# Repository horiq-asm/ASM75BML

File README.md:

HILO8Lを使ってRSTP　wifiカメラ映像で推論を試しました。<br>
python basic_pipelines/detection_s0.py   -i "rtsp://user:passwd@192.168.10.224/stream2"<br>
raspberry pi CM5 搭載基板データです。<br>
Kicadの書式で作成しています。<br>
完成基板の動作はyoutubeでご覧ください<br>
https://youtu.be/_k28zdBtKoo　<br>

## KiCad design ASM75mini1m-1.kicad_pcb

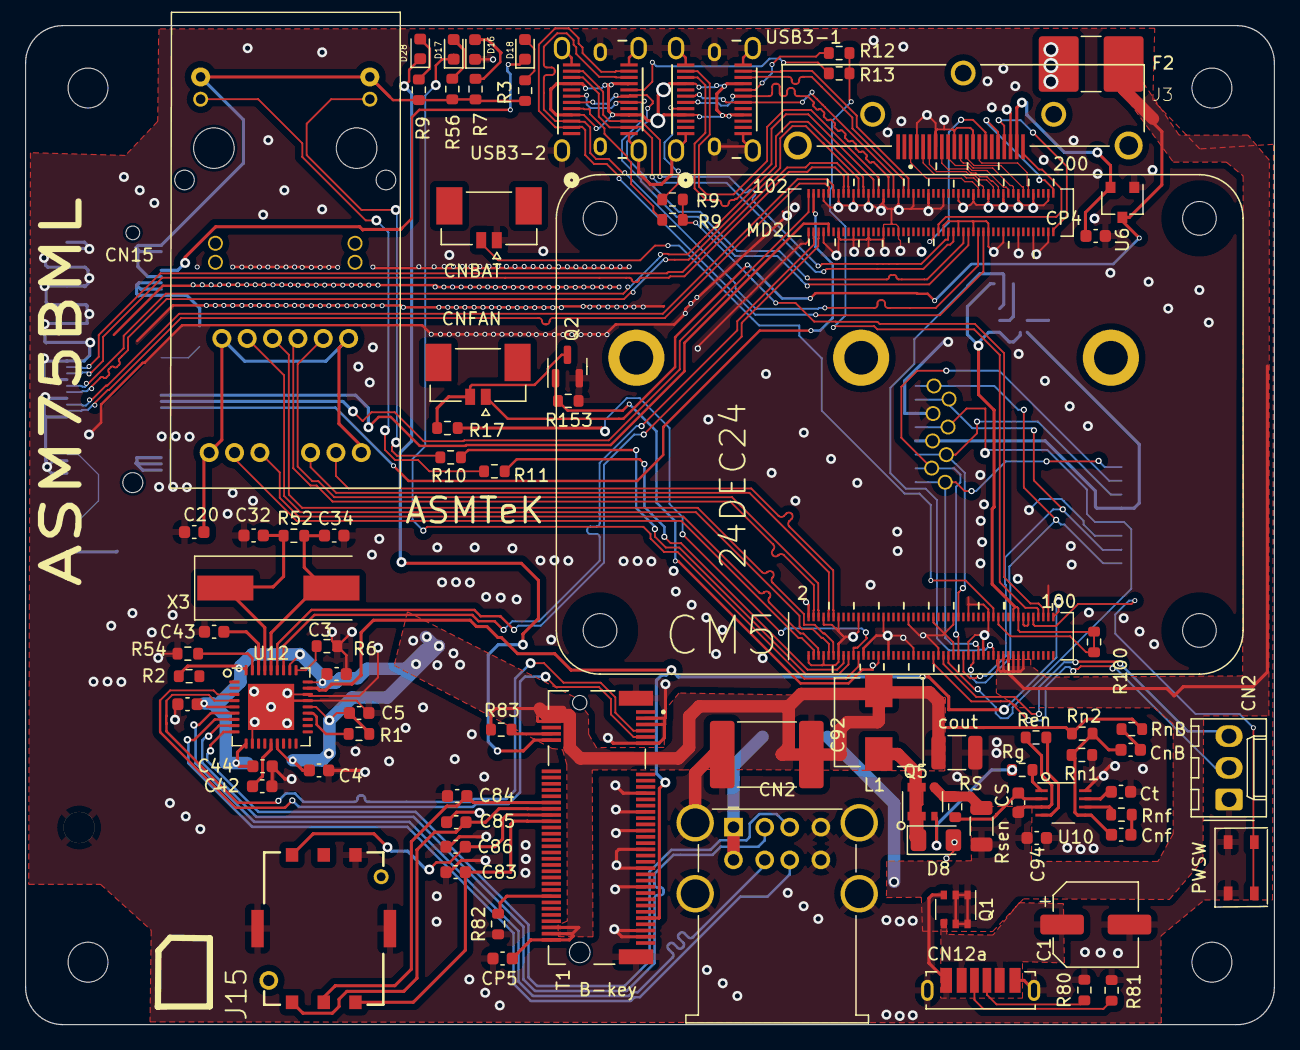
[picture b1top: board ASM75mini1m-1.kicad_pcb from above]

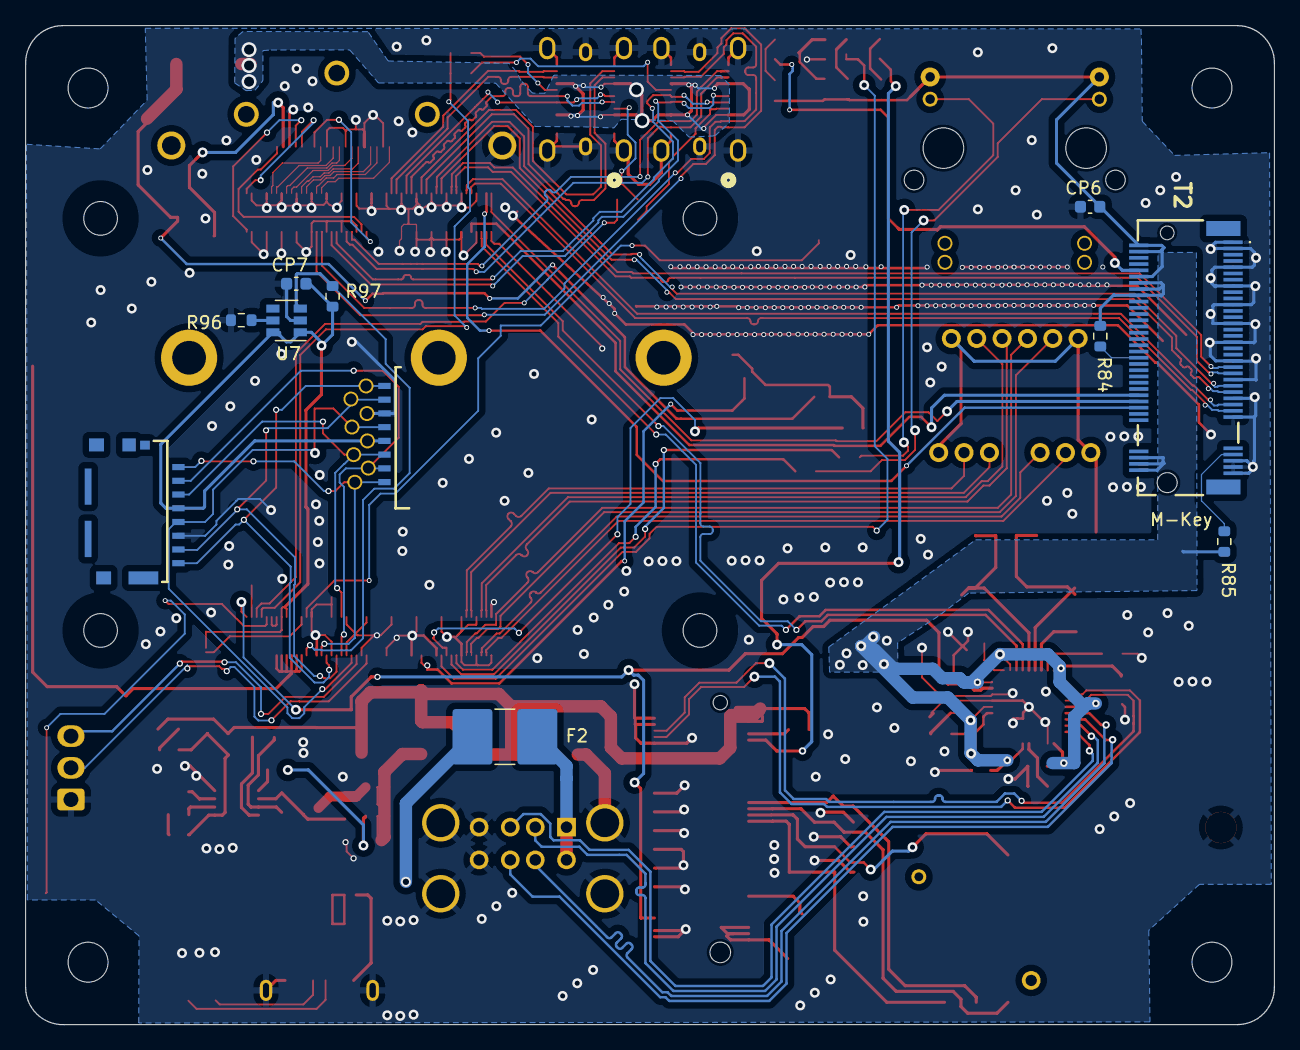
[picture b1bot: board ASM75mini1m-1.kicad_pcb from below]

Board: 2 copper layers, 100.0 x 80.0 mm, 96 parts (11 on the bottom side), 121 nets.

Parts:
C1: RSA0J331MCN1GS; CP_Elec_6.3x5.8
C2, C4, C5, C42, C43, C44: 104; C_0603_1608Metric
C3: 4.7u; C_0603_1608Metric
C20: 0.1u/25V; C_0603_1608Metric
C32, C34: 15ｐ; C_0603_1608Metric
C83, C84, C85, C86: C:2; C_0603_1608Metric
C92: ECASD40J476M025K00; C_2220_5650Metric_Pad1.97x5.40mm_HandSolder
C94: GRM188R61C106MAALD; C_0603_1608Metric
CN2: Molex_KK-254_AE-6410-03A_1x03_P2.54mm_Vertical
CN2#2: USB_A_Wuerth_61400826021_Horizontal_Stacked
CN12a: CUI_UJC-VP-3-SMT-TR
CN15: 0838-1x1t-w7
CNBAT: MOLEX_533980271
CNFAN: MOLEX_533980271
CP4, CP5, CP6, CP7: 104; C_0603_1608Metric
CS: 22n; C_0603_1608Metric
CnB: 220p; C_0603_1608Metric
Cnf: 2.2n; C_0603_1608Metric
Ct: 1n; C_0603_1608Metric
D8: SS2040FL; D_1206_3216Metric
D16: green; LED_0603_1608Metric
D17: red; LED_0603_1608Metric
D18: yellow; LED_0603_1608Metric
D28: blue; LED_0603_1608Metric
F2, F2#2: 0ZCG0075FF2C; R_2816_7142Metric_Pad3.20x4.45mm_HandSolder
J3: SS-53000-003; BEL_SS-53000-003
J4, J4#2: 105162-0001
J15: GCT_SIM8051-6-0-14-01-X-REVD
L1: SRP5020C-R47M; L_Wuerth_HCI-7030
Module1: ComputeModule4; Raspberry-Pi-4-Compute-Module
PWSW: SW_Push; SKRPACE010
Q1, Q5: SSM6J808R; TSOP-6_1.65x3.05mm_P0.95mm
Q2: BSS138-TP; SOT-23
R1, R6: 51k; R_0603_1608Metric
R2, R83, R84, R85: 10k; R_0603_1608Metric
R3, R9, R9#2, R9#3, R10, R11, R12, R13, R56, R82, R153: 1k; R_0603_1608Metric
R7, R80, R81: 5.1k; R_0603_1608Metric
R17: 0; R_0603_1608Metric
R52: 1M; R_0603_1608Metric
R54: 12k; R_0603_1608Metric
R96, R97: 2.2ｋ; R_0603_1608Metric
R100: R:2; R_0603_1608Metric
RS: 20; R_0603_1608Metric
Ren: 10k; R_0603_1608Metric
Rg: 20; R_0603_1608Metric
Rn1: 10k; R_0603_1608Metric
Rn2: 30.9k; R_0603_1608Metric
RnB: 1k; R_0603_1608Metric
Rnf: 8.2k; R_0603_1608Metric
Rsen: 27m; R_1206_3216Metric
T1: 2199230-3; b9973afb-34f9-4941-8c1f-dffebdb6dde0
T2: 1-2199230-5; MDT420M01001
U6: AP2331W; SC-59
U7: BD2222G; SOT-23-6
U10: NJW4160R-TE2; SOT-23-8_Handsoldering
U12: USB2514Bi; QFN-36-1EP_6x6mm_P0.5mm_EP3.7x3.7mm
USB3-1, USB3-2: 12401951E412A_AMP
X3: 24M; Crystal_SMD_HC49-SD
cout: C_1210_3225Metric
h2, h2#2, h2#3, h2#4: MountingHole_3.2mm_M3

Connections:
1.8V: Module1.88 (+1.8v_(Output)), Module1.90 (+1.8v_(Output))
3.3V: C2.1, C3.2, C4.2, C5.1, C44.1, C92.2, CN15.18, CN15.20, CP5.1, CP6.1, L1.1, R1.2, R2.2, R3.1, R7.2, R9.1, R56.2, R83.1, R84.2, R85.1, Rn2.1, RnB.1, T1.2, T1.4, T1.70, T1.72, T1.74, T2.2, T2.4, T2.12, T2.14, T2.16, T2.18, T2.70, T2.72, T2.74, U12.5, U12.10, U12.15, U12.23, U12.27, U12.29, U12.36, cout.1
5VIN: C1.1, CN12a.A9, CN12a.B9, Q1.4
A5: CN12a.A5, R81.1
B5: CN12a.B5, R80.1
CC1: Module1.94 (AnalogIP1), R12.2, R13.2
CC1r1: R12.1, USB3-1.20
CC2: Module1.96 (AnalogIP0), R9#2.2, R9#3.2
CRF: C42.1, U12.14
DEVSLP: R84.1, T2.38
Ethernet_Pair0_N: CN15.10, Module1.10 (Ethernet_Pair0_N)
Ethernet_Pair0_P: CN15.11, Module1.12 (Ethernet_Pair0_P)
Ethernet_Pair1_N: CN15.5, Module1.6 (Ethernet_Pair1_N)
Ethernet_Pair1_P: CN15.4, Module1.4 (Ethernet_Pair1_P)
Ethernet_Pair2_N: CN15.2, Module1.9 (Ethernet_Pair2_N)
Ethernet_Pair2_P: CN15.3, Module1.11 (Ethernet_Pair2_P)
Ethernet_Pair3_N: CN15.9, Module1.5 (Ethernet_Pair3_N)
Ethernet_Pair3_P: CN15.8, Module1.3 (Ethernet_Pair3_P)
Ethernet_nLED2: Module1.17 (Ethernet_nLED2(3.3v)), R10.1
Ethernet_nLED3: Module1.15 (Ethernet_nLED3(3.3v)), R11.1
FAN: CNFAN.2, Q2.3, R17.1
FAN_PWM: Module1.19 (Ethernet_nLED1(3.3v)), R17.2
GND: C1.2, C2.2, C3.1, C4.1, C5.2, C20.2, C32.2, C34.2, C42.2, C43.2, C44.2, C83.2, C84.2, C85.2, C86.2, C92.1, C94.1, CN2.1, CN2#2.4, CN2#2.8, CN2#2.9, CN12a.A12, CN12a.B12, CN12a.S1, CN12a.S2, CNBAT.1, CP4.1, CP5.2, CP6.2, CP7.2, Ct.2, D8.2, D16.1, J3.2, J3.5, J3.8, J3.11, J3.17, J3.S1, J4.6, J4#2.6, J15.6, J15.10, J15.C5, Module1.1 (GND), Module1.2 (GND), Module1.7 (GND), Module1.8 (GND), Module1.13 (GND), Module1.14 (GND), Module1.22 (GND), Module1.23 (GND), Module1.32 (GND), Module1.33 (GND), Module1.42 (GND), Module1.43 (GND), Module1.52 (GND), Module1.53 (GND), Module1.59 (GND), Module1.60 (GND), Module1.65 (GND), Module1.66 (GND), Module1.71 (GND), Module1.74 (GND), Module1.98 (GND), Module1.101 (USB_OTG_ID), Module1.107 (GND), Module1.108 (GND), Module1.113 (GND), Module1.114 (GND), Module1.119 (GND), Module1.120 (GND), Module1.125 (GND), Module1.126 (GND), Module1.131 (GND), Module1.132 (GND), Module1.137 (GND), Module1.138 (GND), Module1.144 (GND), Module1.150 (GND), Module1.155 (GND), Module1.156 (GND), Module1.161 (GND), Module1.162 (GND), Module1.167 (GND), Module1.168 (GND), Module1.173 (GND), Module1.174 (GND), Module1.179 (GND), Module1.180 (GND), Module1.185 (GND), Module1.186 (GND), Module1.191 (GND), Module1.192 (GND), Module1.197 (GND), Module1.198 (GND), PWSW.1, PWSW.2, Q1.3, Q2.2, R6.1, R54.1, R80.2, R81.2, R82.1, R96.1, R153.2, Rn1.2, T1.3, T1.5, T1.11, T1.27, T1.33, T1.39, T1.45, T1.51, T1.57, T1.71, T1.73, T1.S1, T1.S2, T2.1, T2.3, T2.9, T2.15, T2.21, T2.27, T2.33, T2.39, T2.45, T2.51, T2.57, T2.71, T2.73, T2.75, U6.1, U7.2, U10.8, U12.11, U12.24, U12.25, U12.37, USB3-1.1, USB3-1.12, USB3-1.13, USB3-1.24, USB3-1.25, USB3-1.26, USB3-1.27, USB3-1.28, USB3-1.29, USB3-1.30, USB3-2.1, USB3-2.12, USB3-2.13, USB3-2.24, USB3-2.25, USB3-2.26, USB3-2.27, USB3-2.28, USB3-2.29, USB3-2.30, cout.2
GPIO14: CN2.3, Module1.55 (GPIO14)
GPIO15: CN2.2, Module1.51 (GPIO15)
GPIO16: Module1.29 (GPIO16), Q2.1, R153.1
H5V: CP4.2, J3.18, U6.2
HDMI0_CEC: J3.13, Module1.151 (HDMI0_CEC)
HDMI0_CLK_N: J3.12, Module1.190 (HDMI0_CLK_N)
HDMI0_CLK_P: J3.10, Module1.188 (HDMI0_CLK_P)
HDMI0_HOTPLUG: J3.19, Module1.153 (HDMI0_HOTPLUG)
HDMI0_SCL: J3.15, Module1.200 (HDMI0_SCL)
HDMI0_SDA: J3.16, Module1.199 (HDMI0_SDA)
HDMI0_TX0_N: J3.9, Module1.184 (HDMI0_TX0_N)
HDMI0_TX0_P: J3.7, Module1.182 (HDMI0_TX0_P)
HDMI0_TX1_N: J3.6, Module1.178 (HDMI0_TX1_N)
HDMI0_TX1_P: J3.4, Module1.176 (HDMI0_TX1_P)
HDMI0_TX2_N: J3.3, Module1.172 (HDMI0_TX2_N)
HDMI0_TX2_P: J3.1, Module1.170 (HDMI0_TX2_P)
LED2: CN15.19, R10.2
LED3: CN15.17, R11.2
N0010: R83.2, T1.8
N00048: C32.1, R52.2, U12.33, X3.1
N00049: C34.1, R52.1, U12.32, X3.2
N00089: D17.2, R56.1
N00091: D16.2, R7.1
N00095: R96.2, U7.5
N00099: C20.1, CN15.1, CN15.6, CN15.7, CN15.12
N00100: D28.2, R9.2
N00101: D18.2, R3.2
NJ001: Rg.2, U10.1
NJ002: CS.2, RS.2, U10.2
NJ003: CnB.1, RnB.2
NJ004: Cnf.1, Rnf.2
NJ005: CnB.2, Cnf.2, Rn1.1, Rn2.2, U10.5
NJ006: Rnf.1, U10.6
NJ007: Ct.1, U10.7
NJ008: D8.1, L1.2, Q5.1, Q5.2, Q5.5, Q5.6
NJ009: Q5.4, RS.1, Rsen.2
NJ_g: Q5.3, Rg.1
NJen: Ren.2, U10.4
NONrm0: R6.2, U12.28
Nonrm: R1.1, U12.22
PCIe_CLK_N: Module1.112 (PCIe_CLK_N), T2.53
PCIe_CLK_P: Module1.110 (PCIe_CLK_P), T2.55
PCIe_CLK_nREQ: Module1.102 (PCIe_CLK_nREQ), T2.52
PCIe_RX_N: Module1.118 (PCIe_RX_N), T2.41
PCIe_RX_P: Module1.116 (PCIe_RX_P), T2.43
PCIe_TX_N: Module1.124 (PCIe_TX_N), T2.47
PCIe_TX_P: Module1.122 (PCIe_TX_P), T2.49
PCIe_nRST: Module1.109 (PCIe_nRST), T2.50
PCIe_nWAKE: Module1.104 (Reserved), T2.54
PEDET: R85.2, T2.69
PLLF: C43.1, U12.34
PWR_BUT: Module1.92 (RUN_PG), PWSW.3, PWSW.4
Pi_nLED_Activity: D17.1, Module1.21 (PI_nLED_Activity)
RBi: R54.2, U12.35
SD_CLK: J4.5, J4#2.5, Module1.57 (SD_CLK)
SD_CMD: J4.3, J4#2.3, Module1.62 (SD_CMD)
SD_DAT0: J4.7, J4#2.7, Module1.63 (SD_DAT0)
SD_DAT1: J4.8, J4#2.8, Module1.67 (SD_DAT1)
SD_DAT2: J4.1, J4#2.1, Module1.69 (SD_DAT2)
SD_DAT3: J4.2, J4#2.2, Module1.61 (SD_DAT3)
SD_PWR_ON: Module1.75 (SD_PWR_ON), R97.1, U7.3
SD_VDD: J4.4, J4#2.4
SIM_DATE: C86.1, J15.C7, T1.34
SIM_PWR: C83.1, J15.C1, T1.36
SIM_RST: C84.1, J15.C2, T1.30
SIM_SLK: C85.1, J15.C3, T1.32
SIM_SW: R82.2, T1.60
USB3-0-DN: Module1.136 (CAM0_D1_P), USB3-1.7, USB3-1.18
USB3-0-DP: Module1.134 (CAM0_D1_N), USB3-1.6, USB3-1.19
USB3-0-RX_N: Module1.128 (CAM0_D0_N), USB3-1.10
USB3-0-RX_P: Module1.130 (CAM0_D0_P), USB3-1.11
USB3-0-TX_N: Module1.140 (CAM0_C_N), USB3-1.22
USB3-0-TX_P: Module1.142 (CAM0_C_P), USB3-1.23
USB3-1-DN: Module1.165 (DSI0_D1_P), USB3-2.7, USB3-2.18
USB3-1-DP: Module1.163 (DSI0_D1_N), USB3-2.6, USB3-2.19
USB3-1-RX_N: Module1.157 (DSI0_D0_N), USB3-2.11, USB3-2.15
USB3-1-RX_P: Module1.159 (DSI0_D0_P), USB3-2.10, USB3-2.14
USB3-1-TX_N: Module1.169 (DSI0_C_N), USB3-2.3, USB3-2.22
USB3-1-TX_P: Module1.171 (DSI0_C_P), USB3-2.2, USB3-2.23
USB5V: CN2#2.1, CN2#2.5, F2#2.1
USBDM2+: T1.7, U12.4
USBDM2-: T1.9, U12.3
USBDM3+: CN2#2.7, U12.7
USBDM3-: CN2#2.6, U12.6
USBDM4+: CN2#2.3, U12.9
USBDM4-: CN2#2.2, U12.8
USB_N: Module1.103 (USB2_N), U12.30
USB_P: Module1.105 (USB2_P), U12.31
VBAT: CNBAT.2, Module1.76 (Reserved)
VBUS: F2.2, USB3-1.4, USB3-1.9, USB3-1.16, USB3-1.21, USB3-2.4, USB3-2.9, USB3-2.16, USB3-2.21
VCC: CP7.1, Module1.84 (+3.3v_(Output)), Module1.86 (+3.3v_(Output)), R97.2, R100.1, R100.2, U7.1, U7.6
VCC-2: C94.2, CNFAN.1, CS.1, F2.1, F2#2.2, Module1.77 (+5v_(Input)), Module1.79 (+5v_(Input)), Module1.81 (+5v_(Input)), Module1.83 (+5v_(Input)), Module1.85 (+5v_(Input)), Module1.87 (+5v_(Input)), Q1.1, Q1.2, Q1.5, Q1.6, Ren.1, Rsen.1, U6.3, U10.3
WWAN_LED: D28.1, T1.10
cc1r2: R13.1, USB3-2.20
cc2r1: R9#2.1, USB3-1.5
cc2r2: R9#3.1, USB3-2.5
m3das: D18.1, T2.10
nEXTRST: Module1.100 (nEXTRST), T1.67, U12.26

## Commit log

2024-12-28 Create iperf3_speedtest
2024-12-28 Update iperf3_speedtest
